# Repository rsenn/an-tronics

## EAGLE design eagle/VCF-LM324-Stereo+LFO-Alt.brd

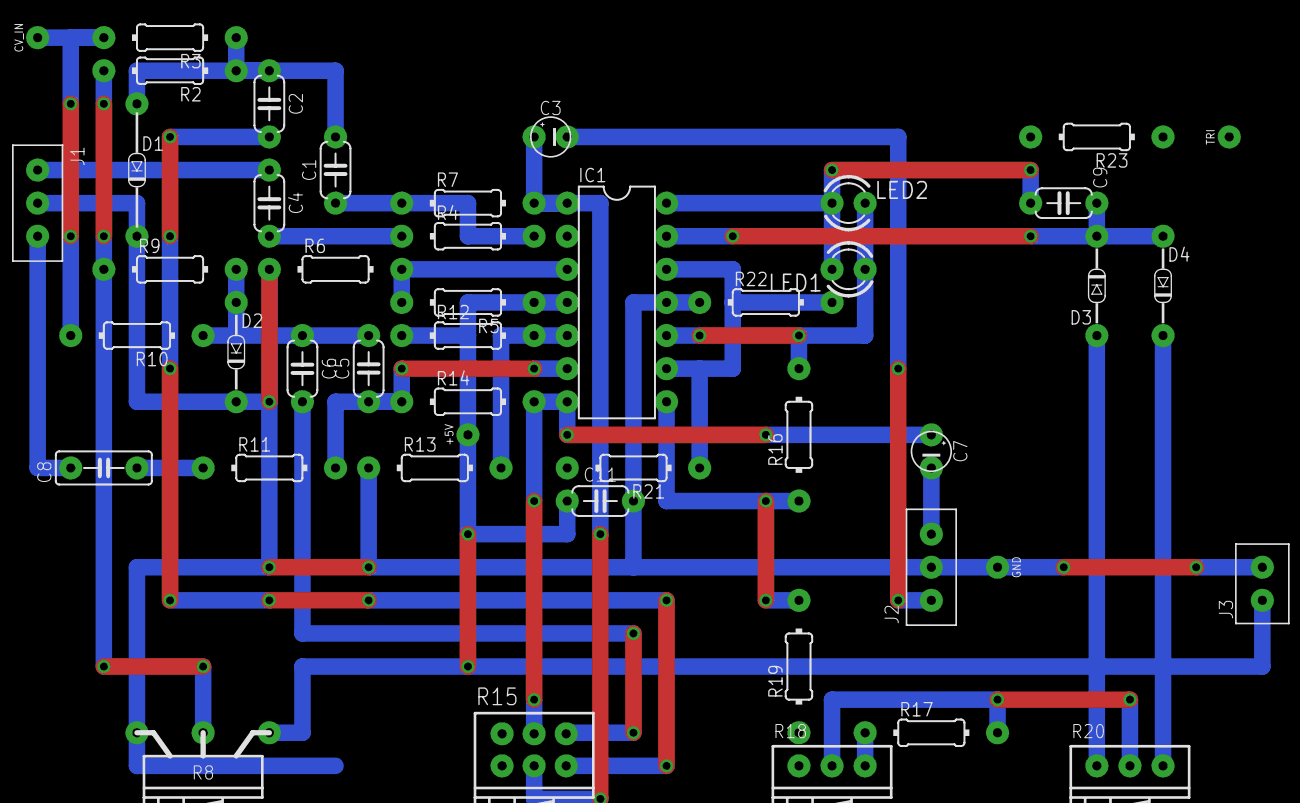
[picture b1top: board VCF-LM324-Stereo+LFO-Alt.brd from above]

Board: 2 copper layers, 46 parts (0 on the bottom side), 31 nets.

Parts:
+5V: VCC; SPAD
C1, C2, C5, C6, C11: 100nF; C050-024X044
C3, C7: 1μF; E2,5-3
C4: 1μF; C050-024X044
C8: 1μF; C050-025X075
C9: 1μF; C050-024X044/V
CV_IN: CV_IN; SPAD
D1: 1N4148; DO34-10V
D2, D3, D4: 1N4148; DO34-7V
GND: GND; SPAD
IC1: LM324; DIL14
J1: A_IN; CONN-3P
J2: A_OUT; CONN-3P
J3: CONN-2P2P/H; CONN-2P
LED1, LED2: LED3MM
R2, R3, R10, R23: 1kΩ; 0204/10
R4, R11: 470kΩ; 0204/10
R5, R6, R7, R12, R13, R14, R21, R22: 100kΩ; 0204/10
R8: POT-P5
R9: 1kΩ; 0204/10-V
R15: POT-STEREO; POT-STEREO-2X3
R16: 47kΩ; 0204/10-V
R17: 4.7kΩ; 0204/10
R18: 10kΩ; POT
R19: 4.7kΩ; 0204/10-V
R20: 100kΩ; POT
TRI: TRIANGLE; SPAD

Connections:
GND: C11.2, D1.C, D2.C, GND.1, IC1.11, J1.2, J2.2, J3.1, R6.1, R8.A, R13.1, R22.1
LEFT_IN: C4.1, J1.1
LEFT_OUT: C3.-, J2.1
unnamed: C1.1, IC1.2, R4.2, R7.1
unnamed: C2.2, R15.1-E
unnamed: C3.+, IC1.1, R7.2, R15.1-S
unnamed: R2.2, R8.S, R9.2
unnamed: IC1.3, R5.2, R6.2
unnamed: CV_IN.1, R3.2, R10.2
unnamed: C1.2, C2.1, D1.A, R2.1, R3.1
unnamed: C4.2, R4.1
unnamed: C6.2, R15.2-E
unnamed: C7.+, IC1.7, R14.2, R15.2-S
unnamed: IC1.5, R12.2, R13.2
unnamed: IC1.8, R16.2, R19.1
unnamed: IC1.10, LED1.A, LED2.K, R16.1
unnamed: C5.2, C6.1, D2.A, R9.1, R10.1
unnamed: C5.1, IC1.6, R11.2, R14.1
unnamed: C8.2, R11.1
unnamed: C9.1, D3.C, D4.A, IC1.13
unnamed: C9.2, IC1.14, LED1.K, LED2.A, R23.2
OA_C_IN+: IC1.9, IC1.12, R21.1, R22.2
RIGHT_IN: C8.1, J1.3
RIGHT_OUT: C7.-, J2.3
TRIM_1_A: D3.A, R20.1
TRIM_1_B: D4.C, R20.3
TRIM_2_A: R17.1, R18.3
TRIM_2_B: R18.1, R19.2
TRIM_P: R17.2, R18.2, R20.2
TRI_OUT: R23.1, TRI.1
VCC: +5V.1, C11.1, IC1.4, J3.2, R5.1, R8.E, R12.1, R21.2

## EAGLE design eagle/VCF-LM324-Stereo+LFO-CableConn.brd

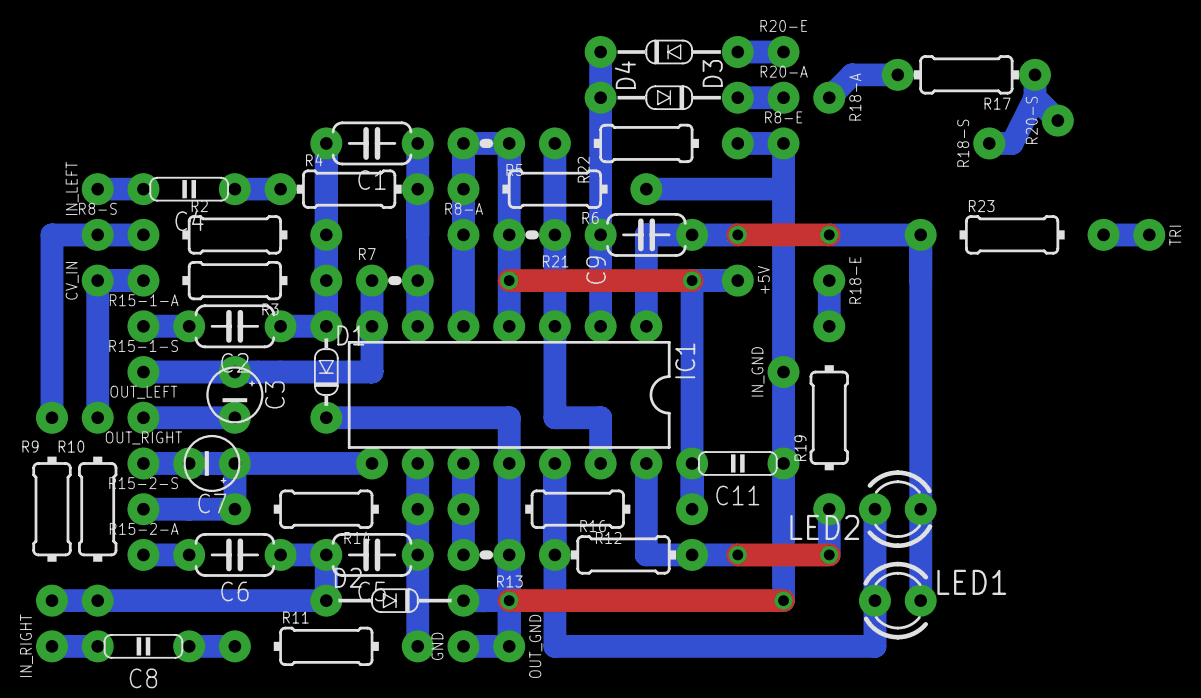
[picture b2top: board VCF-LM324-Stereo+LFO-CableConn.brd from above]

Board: 2 copper layers, 58 parts (0 on the bottom side), 31 nets.

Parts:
+5V: VCC; SPAD
C1, C2, C5, C6: 100nF; C050-024X044
C3, C7: 1μF; E2,5-3
C4, C8: 1μF; C050-020X044
C9: 1μF; C050-024X044/V
C11: 100nF; C050-020X044
CV_IN: CV_IN; SPAD
D1: 1N4148; DO34-5V
D2: 1N4148; DO34-7
D3, D4: 1N4148; DO34-7V
GND: GND; SPAD
IC1: LM324; DIL14
IN_GND: SPAD
IN_LEFT: SPAD
IN_RIGHT: SPAD
LED1, LED2: LED3MM
OUT_GND: SPAD
OUT_LEFT: SPAD
OUT_RIGHT: SPAD
R2, R3, R23: 1kΩ; 0204/10
R4: 470kΩ; 0204/7
R5, R7, R13, R21: 100kΩ; 0204V
R6, R14: 100kΩ; 0204/10
R8-A, R8-E, R8-S, R15-1-A, R15-1-S, R15-2-A, R15-2-S, R18-A, R18-E, R18-S, R20-A, R20-E, R20-S: SPAD
R9, R10: 1kΩ; 0204/10-V
R11: 470kΩ; 0204/10
R12: 100kΩ; 0204/12
R16: 47kΩ; 0204/7
R17: 4.7kΩ; 0204/7-V
R19: 4.7kΩ; 0204/10
R22: 100kΩ; 0204/10-V
TRI: TRIANGLE; SPAD

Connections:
CV_IN: CV_IN.1, R3.2, R10.1
GND: C11.2, D1.C, D2.C, GND.1, IC1.11, IN_GND.1, OUT_GND.1, R6.1, R8-E.1, R13.1, R22.2
LEFT_IN: C4.1, IN_LEFT.1
LEFT_OUT: C3.-, OUT_LEFT.1
unnamed: R17.1, R18-A.1
unnamed: C1.1, IC1.6, R4.2, R7.2
unnamed: C2.2, R15-1-A.1
unnamed: C3.+, IC1.7, R7.1, R15-1-S.1
unnamed: R2.1, R8-S.1, R9.1
unnamed: R18-E.1, R19.2
unnamed: IC1.5, R5.2, R6.2
unnamed: C1.2, C2.1, D1.A, R2.2, R3.1
unnamed: C4.2, R4.1
unnamed: C6.2, R15-2-A.1
unnamed: C7.+, IC1.8, R14.2, R15-2-S.1
unnamed: IC1.10, R12.2, R13.2
unnamed: IC1.14, R16.2, R19.1
unnamed: IC1.12, LED1.A, LED2.K, R16.1
unnamed: C5.2, C6.1, D2.A, R9.2, R10.2
unnamed: C5.1, IC1.9, R11.2, R14.1
unnamed: R23.2, TRI.1
unnamed: C8.2, R11.1
unnamed: C9.1, D3.C, D4.A, IC1.2
unnamed: C9.2, IC1.1, LED1.K, LED2.A, R23.1
OA_C_IN+: IC1.3, IC1.13, R21.1, R22.1
RIGHT_IN: C8.1, IN_RIGHT.1
RIGHT_OUT: C7.-, OUT_RIGHT.1
TRIM_1_A: D3.A, R20-E.1
TRIM_1_B: D4.C, R20-A.1
TRIM_P: R17.2, R18-S.1, R20-S.1
VCC: +5V.1, C11.1, IC1.4, R5.1, R8-A.1, R12.1, R21.2

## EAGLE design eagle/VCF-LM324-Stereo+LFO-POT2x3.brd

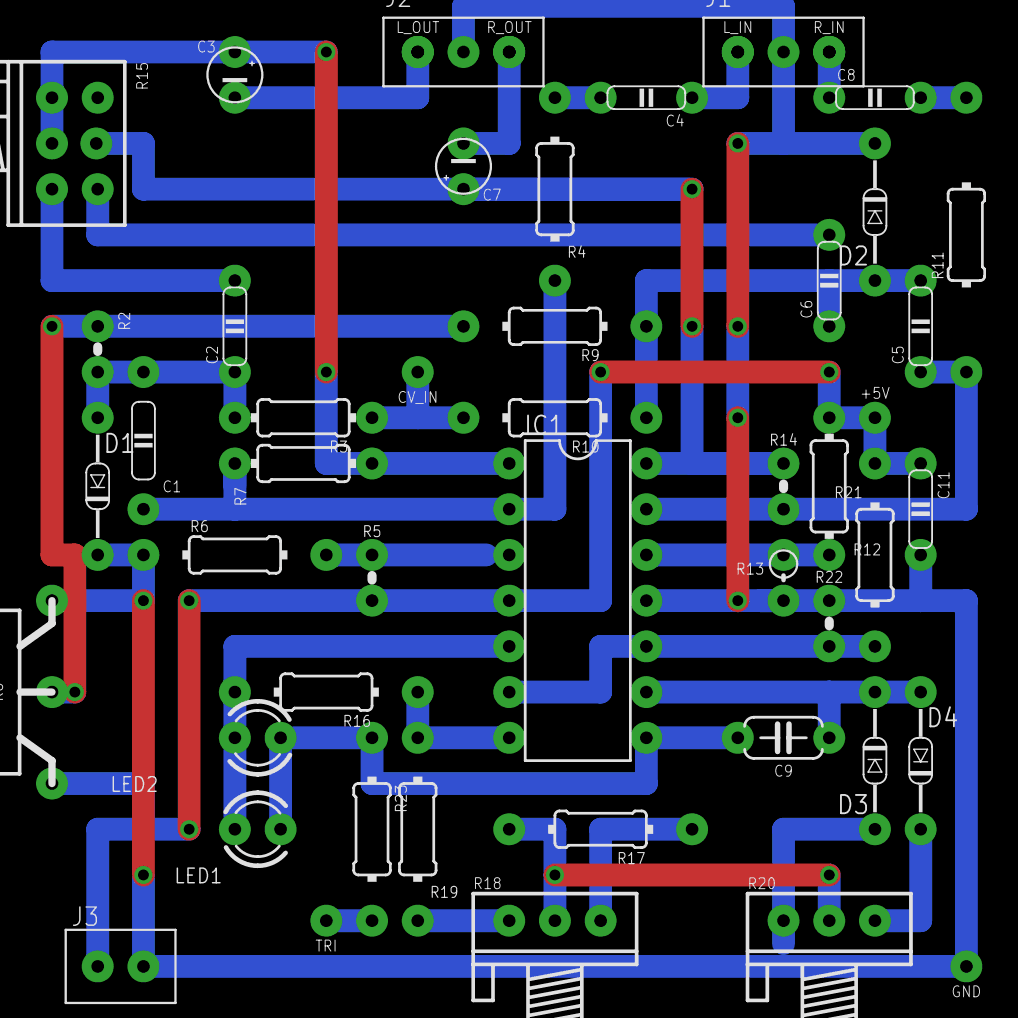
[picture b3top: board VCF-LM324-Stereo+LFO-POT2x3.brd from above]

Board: 2 copper layers, 50 parts (0 on the bottom side), 31 nets.

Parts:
+5V: VCC; SPAD
C1: 0.1μF; C075-020X044/V
C2: 0.1μF; C050-020X044
C3, C7: 1μF; E2,5-3/V
C4, C8: 1μF; C050-020X044
C5, C6, C11: 100nF; C050-020X044
C9: 1μF; C050-024X044
CV_IN: CV_IN; SPAD
D1, D2, D3, D4: 1N4148; DO34-7V
GND: GND; SPAD
IC1: LM324; DIL14
J1: A_IN; CONN-3P
J2: A_OUT; CONN-3P
J3: CONN-2P2P/H; CONN-2P
LED1, LED2: LED3MM
L_IN: AUDIO_IN; SPAD
L_OUT: AUDIO_OUT; SPAD
R2: 1kΩ; 0204V
R3: 1kΩ; 0204/7
R4: 470kΩ; 0204/10-V
R5, R14, R22: 100kΩ; 0204/2V
R6: 100kΩ; 0204/10
R7, R12: 100kΩ; 0204/7-V
R8: POT-P5
R9, R10, R23: 1kΩ; 0204/10
R11: 470kΩ; 0204/15
R13: 100kΩ; 0202V
R15: 10kΩ; POT-STEREO-2X3
R16: 47kΩ; 0204/10
R17: 4.7kΩ; 0204/10
R18: 10kΩ; POT
R19: 4.7kΩ; 0204/10-V
R20: 100kΩ; POT
R21: 100kΩ; 0204/10-V
R_IN: AUDIO_IN; SPAD
R_OUT: AUDIO_OUT; SPAD
TRI: TRIANGLE; SPAD

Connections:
GND: C11.2, D1.C, D2.C, GND.1, IC1.11, J1.2, J2.2, J3.1, R6.1, R8.A, R13.1, R22.1
LEFT_IN: C4.1, J1.1, L_IN.1
LEFT_OUT: C3.-, J2.1, L_OUT.1
unnamed: C6.2, R15.2-E
unnamed: C1.1, IC1.2, R4.1, R7.1
unnamed: C2.2, R15.1-E
unnamed: C3.+, IC1.1, R7.2, R15.1-S
unnamed: R2.1, R8.S, R9.2
unnamed: IC1.3, R5.1, R6.2
unnamed: CV_IN.1, R3.1, R10.2
unnamed: C1.2, C2.1, D1.A, R2.2, R3.2
unnamed: C4.2, R4.2
unnamed: C7.+, IC1.14, R14.1, R15.2-S
unnamed: IC1.12, R12.1, R13.2
unnamed: IC1.7, R16.1, R19.2
unnamed: IC1.5, LED1.A, LED2.K, R16.2
unnamed: C5.2, C6.1, D2.A, R9.1, R10.1
unnamed: C5.1, IC1.13, R11.1, R14.2
unnamed: C8.2, R11.2
unnamed: C9.1, D3.C, D4.A, IC1.9
unnamed: C9.2, IC1.8, LED1.K, LED2.A, R23.1
OA_C_IN+: IC1.6, IC1.10, R21.2, R22.2
RIGHT_IN: C8.1, J1.3, R_IN.1
RIGHT_OUT: C7.-, J2.3, R_OUT.1
TRIM_1_A: D3.A, R20.1
TRIM_1_B: D4.C, R20.3
TRIM_2_A: R17.1, R18.3
TRIM_2_B: R18.1, R19.1
TRIM_P: R17.2, R18.2, R20.2
TRI_OUT: R23.2, TRI.1
VCC: +5V.1, C11.1, IC1.4, J3.2, R5.2, R8.E, R12.2, R21.1
